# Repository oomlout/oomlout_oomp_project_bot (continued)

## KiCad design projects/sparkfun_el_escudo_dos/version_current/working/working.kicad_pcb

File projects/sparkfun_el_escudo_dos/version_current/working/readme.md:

# EL_Escudo_Dos by sparkfun  
This is a harvested standardized copy of a project from github.  
The original project can be found at:  
https://github.com/sparkfun/EL_Escudo_Dos  
Please consult that link for additional, details, files, and license information.  
Note: It was auto harvested and if the original repo had more than one board file or anything out of the ordinary the files here are likely not representative.

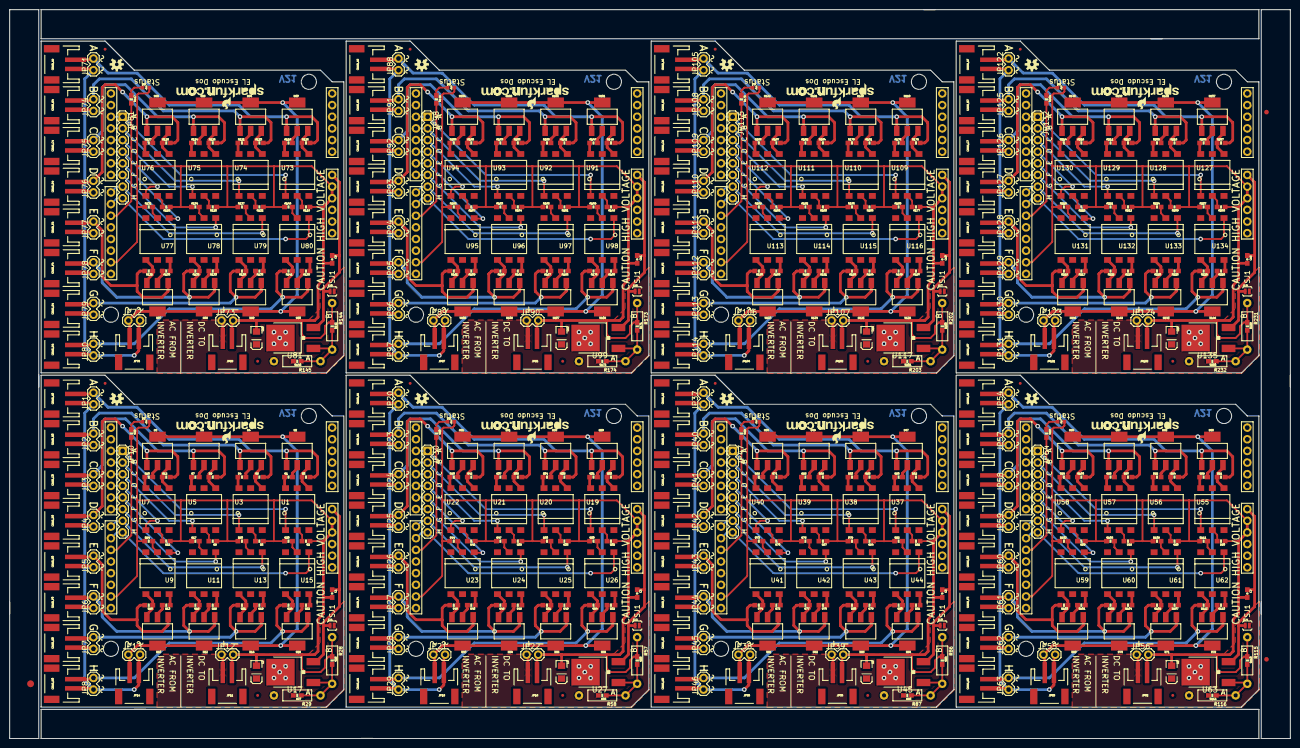
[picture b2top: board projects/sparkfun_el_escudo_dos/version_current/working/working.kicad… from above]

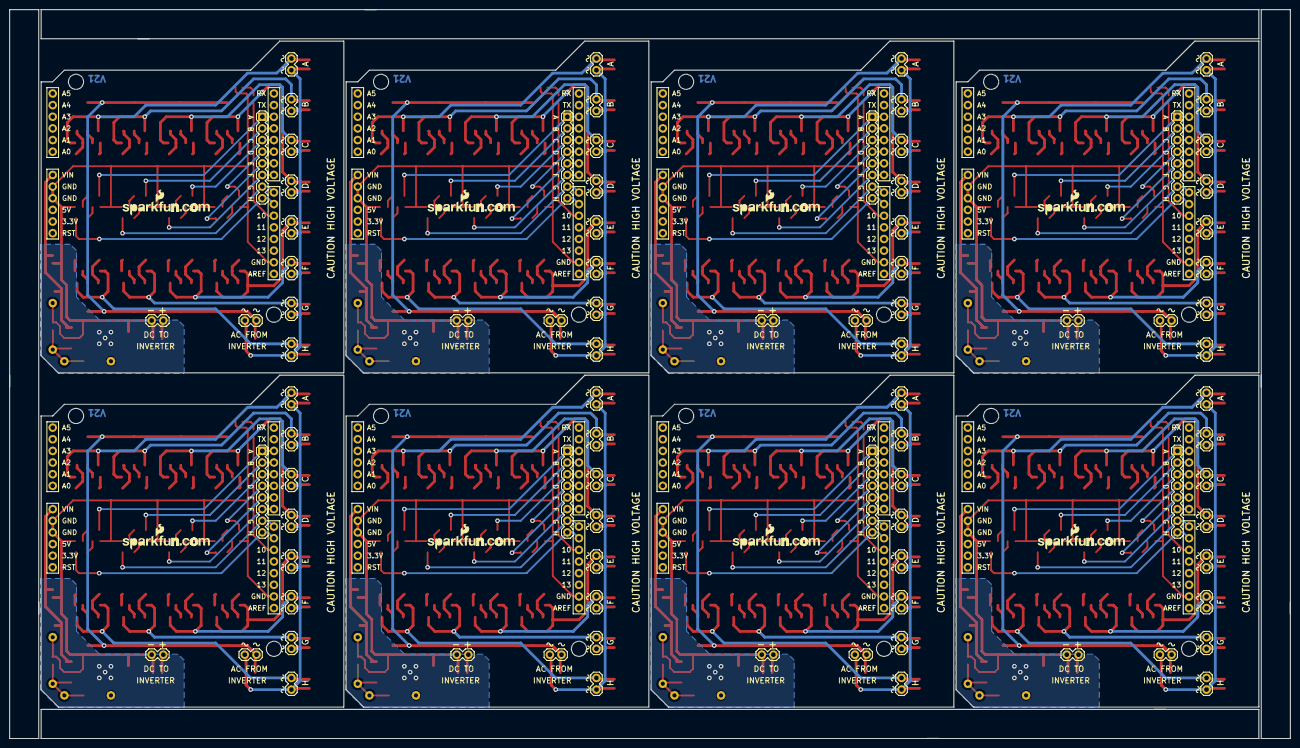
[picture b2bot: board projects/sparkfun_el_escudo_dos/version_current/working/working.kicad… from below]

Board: 2 copper layers, 279.4 x 159.0 mm, 619 parts (8 on the bottom side), 448 nets.

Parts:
C1, C3, C5, C7, C9, C11, C13, C15: 0.1uF; 0603-CAP
C2, C4, C6, C8, C10, C12, C14, C16: 10uF; EIA3216
CHAN_A0, CHAN_A1, CHAN_A2, CHAN_A3, CHAN_A4, CHAN_A5, CHAN_A6, CHAN_A7: JST-2-SMD
CHAN_B0, CHAN_B1, CHAN_B2, CHAN_B3, CHAN_B4, CHAN_B5, CHAN_B6, CHAN_B7: JST-2-SMD
CHAN_C0, CHAN_C1, CHAN_C2, CHAN_C3, CHAN_C4, CHAN_C5, CHAN_C6, CHAN_C7: JST-2-SMD
CHAN_D0, CHAN_D1, CHAN_D2, CHAN_D3, CHAN_D4, CHAN_D5, CHAN_D6, CHAN_D7: JST-2-SMD
CHAN_E0, CHAN_E1, CHAN_E2, CHAN_E3, CHAN_E4, CHAN_E5, CHAN_E6, CHAN_E7: JST-2-SMD
CHAN_F0, CHAN_F1, CHAN_F2, CHAN_F3, CHAN_F4, CHAN_F5, CHAN_F6, CHAN_F7: JST-2-SMD
CHAN_G0, CHAN_G1, CHAN_G2, CHAN_G3, CHAN_G4, CHAN_G5, CHAN_G6, CHAN_G7: JST-2-SMD
CHAN_H0, CHAN_H1, CHAN_H2, CHAN_H3, CHAN_H4, CHAN_H5, CHAN_H6, CHAN_H7: JST-2-SMD
D1, D2, D3, D4, D5, D6, D7, D8: Status; LED-0603
E$1: FIDUCIAL-1.5X3
E$5, E$6: FIDUCIAL-1X2
JP1, JP2, JP3, JP4, JP5, JP6, JP7, JP8, JP12, JP13, JP20, JP21, JP22, JP23, JP24, JP25, JP26, JP27, JP28, JP29, JP37, JP38, JP39, JP40, JP41, JP42, JP43, JP44, JP45, JP46, JP54, JP55, JP56, JP57, JP58, JP59, JP60, JP61, JP62, JP63, JP71, JP72, JP73, JP74, JP75, JP76, JP77, JP78, JP79, JP80, JP88, JP89, JP90, JP91, JP92, JP93, JP94, JP95, JP96, JP97, JP105, JP106, JP107, JP108, JP109, JP110, JP111, JP112, JP113, JP114, JP122, JP123, JP124, JP125, JP126, JP127, JP128, JP129, JP130, JP131: 1X02
JP9, JP15, JP31, JP32, JP48, JP49, JP65, JP66, JP82, JP83, JP99, JP100, JP116, JP117, JP133, JP134: LOGO-SFENEW; SFE-NEW-WEBLOGO
JP10, JP30, JP47, JP64, JP81, JP98, JP115, JP132: 1X08
JP11, JP14, JP18, JP19, JP35, JP36, JP52, JP53, JP69, JP70, JP86, JP87, JP103, JP104, JP120, JP121: JST-2-SMD
JP16, JP17, JP33, JP34, JP50, JP51, JP67, JP68, JP84, JP85, JP101, JP102, JP118, JP119, JP135, JP136: FIDUCIALUFIDUCIAL; MICRO-FIDUCIAL
R1, R3, R4, R6, R7, R9, R10, R12, R13, R15, R16, R18, R19, R21, R22, R24, R25, R30, R31, R33, R34, R36, R37, R39, R40, R42, R43, R45, R46, R48, R49, R51, R52, R54, R59, R60, R62, R63, R65, R66, R68, R69, R71, R72, R74, R75, R77, R78, R80, R81, R83, R88, R89, R91, R92, R94, R95, R97, R98, R100, R101, R103, R104, R106, R107, R109, R110, R112, R117, R118, R120, R121, R123, R124, R126, R127, R129, R130, R132, R133, R135, R136, R138, R139, R141, R146, R147, R149, R150, R152, R153, R155, R156, R158, R159, R161, R162, R164, R165, R167, R168, R170, R175, R176, R178, R179, R181, R182, R184, R185, R187, R188, R190, R191, R193, R194, R196, R197, R199, R204, R205, R207, R208, R210, R211, R213, R214, R216, R217, R219, R220, R222, R223, R225, R226, R228: 330; 0603-RES
R2, R5, R8, R11, R14, R17, R20, R23, R26, R32, R35, R38, R41, R44, R47, R50, R53, R55, R61, R64, R67, R70, R73, R76, R79, R82, R84, R90, R93, R96, R99, R102, R105, R108, R111, R113, R119, R122, R125, R128, R131, R134, R137, R140, R142, R148, R151, R154, R157, R160, R163, R166, R169, R171, R177, R180, R183, R186, R189, R192, R195, R198, R200, R206, R209, R212, R215, R218, R221, R224, R227, R229: 390; 0603-RES
R27, R56, R85, R114, R143, R172, R201, R230: 240; 0603-RES
R28, R57, R86, R115, R144, R173, R202, R231: B; AXIAL-0.4
R29, R58, R87, R116, R145, R174, R203, R232: A; AXIAL-0.4
SJ1, SJ2, SJ3, SJ4, SJ5, SJ6, SJ7, SJ8: SJ_2S-NO
U1, U3, U5, U7, U9, U11, U13, U15, U19, U20, U21, U22, U23, U24, U25, U26, U37, U38, U39, U40, U41, U42, U43, U44, U55, U56, U57, U58, U59, U60, U61, U62, U73, U74, U75, U76, U77, U78, U79, U80, U91, U92, U93, U94, U95, U96, U97, U98, U109, U110, U111, U112, U113, U114, U115, U116, U127, U128, U129, U130, U131, U132, U133, U134: MOC3063S; DIP8SMD
U2, U4, U6, U8, U10, U12, U14, U16, U29, U30, U31, U32, U33, U34, U35, U36, U47, U48, U49, U50, U51, U52, U53, U54, U65, U66, U67, U68, U69, U70, U71, U72, U83, U84, U85, U86, U87, U88, U89, U90, U101, U102, U103, U104, U105, U106, U107, U108, U119, U120, U121, U122, U123, U124, U125, U126, U137, U138, U139, U140, U141, U142, U143, U144: Z0103MN; SOT223
U17, U27, U45, U63, U81, U99, U117, U135: LM317; V-REG_DPACK
U18, U28, U46, U64, U82, U100, U118, U136: ARDUINO_SHIELD; DUEMILANOVE_SHIELD_NOLABELS
U$1, U$2, U$3, U$4, U$5, U$6, U$7, U$8: OSHW-LOGOS; OSHW-LOGO-S

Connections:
EL_A: JP10.1, U1.1, U18.D2
EL_A1: JP30.1, U19.1, U28.D2
EL_A2: JP47.1, U37.1, U46.D2
EL_A3: JP64.1, U55.1, U64.D2
EL_A4: JP81.1, U73.1, U82.D2
EL_A5: JP98.1, U91.1, U100.D2
EL_A6: JP115.1, U109.1, U118.D2
EL_A7: JP132.1, U127.1, U136.D2
EL_B: JP10.2, U3.1, U18.D3
EL_B1: JP30.2, U20.1, U28.D3
EL_B2: JP47.2, U38.1, U46.D3
EL_B3: JP64.2, U56.1, U64.D3
EL_B4: JP81.2, U74.1, U82.D3
EL_B5: JP98.2, U92.1, U100.D3
EL_B6: JP115.2, U110.1, U118.D3
EL_B7: JP132.2, U128.1, U136.D3
EL_C: JP10.3, U5.1, U18.D4
EL_C1: JP30.3, U21.1, U28.D4
EL_C2: JP47.3, U39.1, U46.D4
EL_C3: JP64.3, U57.1, U64.D4
EL_C4: JP81.3, U75.1, U82.D4
EL_C5: JP98.3, U93.1, U100.D4
EL_C6: JP115.3, U111.1, U118.D4
EL_C7: JP132.3, U129.1, U136.D4
EL_D: JP10.4, U7.1, U18.D5
EL_D1: JP30.4, U22.1, U28.D5
EL_D2: JP47.4, U40.1, U46.D5
EL_D3: JP64.4, U58.1, U64.D5
EL_D4: JP81.4, U76.1, U82.D5
EL_D5: JP98.4, U94.1, U100.D5
EL_D6: JP115.4, U112.1, U118.D5
EL_D7: JP132.4, U130.1, U136.D5
EL_E: JP10.5, U9.1, U18.D6
EL_E1: JP30.5, U23.1, U28.D6
EL_E2: JP47.5, U41.1, U46.D6
EL_E3: JP64.5, U59.1, U64.D6
EL_E4: JP81.5, U77.1, U82.D6
EL_E5: JP98.5, U95.1, U100.D6
EL_E6: JP115.5, U113.1, U118.D6
EL_E7: JP132.5, U131.1, U136.D6
EL_F: JP10.6, U11.1, U18.D7
EL_F1: JP30.6, U24.1, U28.D7
EL_F2: JP47.6, U42.1, U46.D7
EL_F3: JP64.6, U60.1, U64.D7
EL_F4: JP81.6, U78.1, U82.D7
EL_F5: JP98.6, U96.1, U100.D7
EL_F6: JP115.6, U114.1, U118.D7
EL_F7: JP132.6, U132.1, U136.D7
EL_G: JP10.7, U13.1, U18.D8
EL_G1: JP30.7, U25.1, U28.D8
EL_G2: JP47.7, U43.1, U46.D8
EL_G3: JP64.7, U61.1, U64.D8
EL_G4: JP81.7, U79.1, U82.D8
EL_G5: JP98.7, U97.1, U100.D8
EL_G6: JP115.7, U115.1, U118.D8
EL_G7: JP132.7, U133.1, U136.D8
EL_H: JP10.8, U15.1, U18.D9
EL_H1: JP30.8, U26.1, U28.D9
EL_H2: JP47.8, U44.1, U46.D9
EL_H3: JP64.8, U62.1, U64.D9
EL_H4: JP81.8, U80.1, U82.D9
EL_H5: JP98.8, U98.1, U100.D9
EL_H6: JP115.8, U116.1, U118.D9
EL_H7: JP132.8, U134.1, U136.D9
GND: C1.2, C2.C, D1.C, JP11.1, JP12.2, R2.1, R5.1, R8.1, R11.1, R14.1, R17.1, R20.1, R23.1, R26.1, R28.P$1, U18.GND@0, U18.GND@1, U18.GND@2
GND1: C3.2, C4.C, D2.C, JP18.1, JP22.2, R32.1, R35.1, R38.1, R41.1, R44.1, R47.1, R50.1, R53.1, R55.1, R57.P$1, U28.GND@0, U28.GND@1, U28.GND@2
GND2: C5.2, C6.C, D3.C, JP35.1, JP39.2, R61.1, R64.1, R67.1, R70.1, R73.1, R76.1, R79.1, R82.1, R84.1, R86.P$1, U46.GND@0, U46.GND@1, U46.GND@2
GND3: C7.2, C8.C, D4.C, JP52.1, JP56.2, R90.1, R93.1, R96.1, R99.1, R102.1, R105.1, R108.1, R111.1, R113.1, R115.P$1, U64.GND@0, U64.GND@1, U64.GND@2
GND4: C9.2, C10.C, D5.C, JP69.1, JP73.2, R119.1, R122.1, R125.1, R128.1, R131.1, R134.1, R137.1, R140.1, R142.1, R144.P$1, U82.GND@0, U82.GND@1, U82.GND@2
GND5: C11.2, C12.C, D6.C, JP86.1, JP90.2, R148.1, R151.1, R154.1, R157.1, R160.1, R163.1, R166.1, R169.1, R171.1, R173.P$1, U100.GND@0, U100.GND@1, U100.GND@2
GND6: C13.2, C14.C, D7.C, JP103.1, JP107.2, R177.1, R180.1, R183.1, R186.1, R189.1, R192.1, R195.1, R198.1, R200.1, R202.P$1, U118.GND@0, U118.GND@1, U118.GND@2
GND7: C15.2, C16.C, D8.C, JP120.1, JP124.2, R206.1, R209.1, R212.1, R215.1, R218.1, R221.1, R224.1, R227.1, R229.1, R231.P$1, U136.GND@0, U136.GND@1, U136.GND@2
HV: JP13.1, JP14.2, U2.4, U4.4, U6.4, U8.4, U10.4, U12.4, U14.4, U16.4
HV1: JP19.2, JP21.1, U29.4, U30.4, U31.4, U32.4, U33.4, U34.4, U35.4, U36.4
HV2: JP36.2, JP38.1, U47.4, U48.4, U49.4, U50.4, U51.4, U52.4, U53.4, U54.4
HV3: JP53.2, JP55.1, U65.4, U66.4, U67.4, U68.4, U69.4, U70.4, U71.4, U72.4
HV4: JP70.2, JP72.1, U83.4, U84.4, U85.4, U86.4, U87.4, U88.4, U89.4, U90.4
HV5: JP87.2, JP89.1, U101.4, U102.4, U103.4, U104.4, U105.4, U106.4, U107.4, U108.4
HV6: JP104.2, JP106.1, U119.4, U120.4, U121.4, U122.4, U123.4, U124.4, U125.4, U126.4
HV7: JP121.2, JP123.1, U137.4, U138.4, U139.4, U140.4, U141.4, U142.4, U143.4, U144.4
HVGND: CHAN_A0.1, CHAN_B0.1, CHAN_C0.1, CHAN_D0.1, CHAN_E0.1, CHAN_F0.1, CHAN_G0.1, CHAN_H0.1, JP1.1, JP2.1, JP3.1, JP4.1, JP5.1, JP6.1, JP7.1, JP8.1, JP13.2, JP14.1
HVGND1: CHAN_A1.1, CHAN_B1.1, CHAN_C1.1, CHAN_D1.1, CHAN_E1.1, CHAN_F1.1, CHAN_G1.1, CHAN_H1.1, JP19.1, JP20.1, JP21.2, JP23.1, JP24.1, JP25.1, JP26.1, JP27.1, JP28.1, JP29.1
HVGND2: CHAN_A2.1, CHAN_B2.1, CHAN_C2.1, CHAN_D2.1, CHAN_E2.1, CHAN_F2.1, CHAN_G2.1, CHAN_H2.1, JP36.1, JP37.1, JP38.2, JP40.1, JP41.1, JP42.1, JP43.1, JP44.1, JP45.1, JP46.1
HVGND3: CHAN_A3.1, CHAN_B3.1, CHAN_C3.1, CHAN_D3.1, CHAN_E3.1, CHAN_F3.1, CHAN_G3.1, CHAN_H3.1, JP53.1, JP54.1, JP55.2, JP57.1, JP58.1, JP59.1, JP60.1, JP61.1, JP62.1, JP63.1
HVGND4: CHAN_A4.1, CHAN_B4.1, CHAN_C4.1, CHAN_D4.1, CHAN_E4.1, CHAN_F4.1, CHAN_G4.1, CHAN_H4.1, JP70.1, JP71.1, JP72.2, JP74.1, JP75.1, JP76.1, JP77.1, JP78.1, JP79.1, JP80.1
HVGND5: CHAN_A5.1, CHAN_B5.1, CHAN_C5.1, CHAN_D5.1, CHAN_E5.1, CHAN_F5.1, CHAN_G5.1, CHAN_H5.1, JP87.1, JP88.1, JP89.2, JP91.1, JP92.1, JP93.1, JP94.1, JP95.1, JP96.1, JP97.1
HVGND6: CHAN_A6.1, CHAN_B6.1, CHAN_C6.1, CHAN_D6.1, CHAN_E6.1, CHAN_F6.1, CHAN_G6.1, CHAN_H6.1, JP104.1, JP105.1, JP106.2, JP108.1, JP109.1, JP110.1, JP111.1, JP112.1, JP113.1, JP114.1
HVGND7: CHAN_A7.1, CHAN_B7.1, CHAN_C7.1, CHAN_D7.1, CHAN_E7.1, CHAN_F7.1, CHAN_G7.1, CHAN_H7.1, JP121.1, JP122.1, JP123.2, JP125.1, JP126.1, JP127.1, JP128.1, JP129.1, JP130.1, JP131.1
INV: C2.A, JP11.2, JP12.1, R27.2, R29.P$2, SJ1.2, U17.4
INV1: C4.A, JP18.2, JP22.1, R56.2, R58.P$2, SJ2.2, U27.4
INV2: C6.A, JP35.2, JP39.1, R85.2, R87.P$2, SJ3.2, U45.4
INV3: C8.A, JP52.2, JP56.1, R114.2, R116.P$2, SJ4.2, U63.4
INV4: C10.A, JP69.2, JP73.1, R143.2, R145.P$2, SJ5.2, U81.4
INV5: C12.A, JP86.2, JP90.1, R172.2, R174.P$2, SJ6.2, U99.4
INV6: C14.A, JP103.2, JP107.1, R201.2, R203.P$2, SJ7.2, U117.4
INV7: C16.A, JP120.2, JP124.1, R230.2, R232.P$2, SJ8.2, U135.4
unnamed: R2.2, U1.2
unnamed: R26.2, R27.1, R28.P$2, R29.P$1, U17.1
unnamed: R1.1, U1.6
unnamed: R25.2, U18.D10
unnamed: R6.1, U3.4, U4.3
unnamed: R5.2, U3.2
unnamed: R4.1, U3.6
unnamed: CHAN_B0.2, JP2.2, R6.2, U4.1
unnamed: R1.2, U2.2
unnamed: R9.1, U5.4, U6.3
unnamed: R8.2, U5.2
unnamed: R7.1, U5.6
unnamed: CHAN_C0.2, JP3.2, R9.2, U6.1
unnamed: D1.A, R25.1
unnamed: R4.2, U4.2
unnamed: R12.1, U7.4, U8.3
unnamed: R11.2, U7.2
unnamed: R10.1, U7.6
unnamed: CHAN_D0.2, JP4.2, R12.2, U8.1
unnamed: R7.2, U6.2
unnamed: CHAN_A0.2, JP1.2, R3.2, U2.1
unnamed: R15.1, U9.4, U10.3
unnamed: R14.2, U9.2
unnamed: R13.1, U9.6
unnamed: CHAN_E0.2, JP5.2, R15.2, U10.1
unnamed: R10.2, U8.2
unnamed: R18.1, U11.4, U12.3
unnamed: R17.2, U11.2
unnamed: R16.1, U11.6
unnamed: CHAN_F0.2, JP6.2, R18.2, U12.1
unnamed: R13.2, U10.2
unnamed: R21.1, U13.4, U14.3
unnamed: R20.2, U13.2
unnamed: R19.1, U13.6
unnamed: CHAN_G0.2, JP7.2, R21.2, U14.1
unnamed: R16.2, U12.2
unnamed: R24.1, U15.4, U16.3
unnamed: R23.2, U15.2
unnamed: R22.1, U15.6
unnamed: CHAN_H0.2, JP8.2, R24.2, U16.1
unnamed: R19.2, U14.2
unnamed: R22.2, U16.2
unnamed: D2.A, R30.1
unnamed: R33.1, U19.4, U29.3
unnamed: R32.2, U19.2
unnamed: R31.1, U19.6
unnamed: CHAN_A1.2, JP20.2, R33.2, U29.1
unnamed: R36.1, U20.4, U30.3
unnamed: R35.2, U20.2
unnamed: R34.1, U20.6
unnamed: CHAN_B1.2, JP23.2, R36.2, U30.1
unnamed: R39.1, U21.4, U31.3
unnamed: R38.2, U21.2
unnamed: R37.1, U21.6
unnamed: CHAN_C1.2, JP24.2, R39.2, U31.1
unnamed: R42.1, U22.4, U32.3
unnamed: R41.2, U22.2
unnamed: R40.1, U22.6
unnamed: CHAN_D1.2, JP25.2, R42.2, U32.1
unnamed: R45.1, U23.4, U33.3
unnamed: R44.2, U23.2
unnamed: R43.1, U23.6
unnamed: CHAN_E1.2, JP26.2, R45.2, U33.1
unnamed: R48.1, U24.4, U34.3
unnamed: R47.2, U24.2
unnamed: R46.1, U24.6
unnamed: CHAN_F1.2, JP27.2, R48.2, U34.1
unnamed: R51.1, U25.4, U35.3
unnamed: R50.2, U25.2
unnamed: R49.1, U25.6
unnamed: CHAN_G1.2, JP28.2, R51.2, U35.1
unnamed: R54.1, U26.4, U36.3
unnamed: R53.2, U26.2
unnamed: R52.1, U26.6
unnamed: CHAN_H1.2, JP29.2, R54.2, U36.1
unnamed: R55.2, R56.1, R57.P$2, R58.P$1, U27.1
unnamed: R31.2, U29.2
unnamed: R34.2, U30.2
unnamed: R37.2, U31.2
unnamed: R40.2, U32.2
unnamed: R43.2, U33.2
unnamed: R46.2, U34.2
unnamed: R49.2, U35.2
unnamed: R52.2, U36.2
unnamed: R30.2, U28.D10
unnamed: D3.A, R59.1
unnamed: R62.1, U37.4, U47.3
unnamed: R61.2, U37.2
unnamed: R60.1, U37.6
unnamed: CHAN_A2.2, JP37.2, R62.2, U47.1
unnamed: R65.1, U38.4, U48.3
unnamed: R64.2, U38.2
unnamed: R63.1, U38.6
unnamed: CHAN_B2.2, JP40.2, R65.2, U48.1
unnamed: R68.1, U39.4, U49.3
unnamed: R67.2, U39.2
unnamed: R66.1, U39.6
unnamed: CHAN_C2.2, JP41.2, R68.2, U49.1
unnamed: R71.1, U40.4, U50.3
unnamed: R70.2, U40.2
unnamed: R69.1, U40.6
unnamed: CHAN_D2.2, JP42.2, R71.2, U50.1
unnamed: R74.1, U41.4, U51.3
unnamed: R73.2, U41.2
unnamed: R72.1, U41.6
unnamed: CHAN_E2.2, JP43.2, R74.2, U51.1
unnamed: R77.1, U42.4, U52.3
unnamed: R76.2, U42.2
unnamed: R75.1, U42.6
unnamed: CHAN_F2.2, JP44.2, R77.2, U52.1
unnamed: R80.1, U43.4, U53.3
unnamed: R79.2, U43.2
unnamed: R78.1, U43.6
unnamed: CHAN_G2.2, JP45.2, R80.2, U53.1
unnamed: R83.1, U44.4, U54.3
unnamed: R82.2, U44.2
unnamed: R3.1, U1.4, U2.3
unnamed: R81.1, U44.6
unnamed: CHAN_H2.2, JP46.2, R83.2, U54.1
unnamed: R84.2, R85.1, R86.P$2, R87.P$1, U45.1
unnamed: R60.2, U47.2
unnamed: R63.2, U48.2
unnamed: R66.2, U49.2
unnamed: R69.2, U50.2
unnamed: R72.2, U51.2
unnamed: R75.2, U52.2
unnamed: R78.2, U53.2
unnamed: R81.2, U54.2
unnamed: R59.2, U46.D10
unnamed: D4.A, R88.1
unnamed: R91.1, U55.4, U65.3
unnamed: R90.2, U55.2
unnamed: R89.1, U55.6
unnamed: CHAN_A3.2, JP54.2, R91.2, U65.1
unnamed: R94.1, U56.4, U66.3
unnamed: R93.2, U56.2
unnamed: R92.1, U56.6
unnamed: CHAN_B3.2, JP57.2, R94.2, U66.1
unnamed: R97.1, U57.4, U67.3
unnamed: R96.2, U57.2
unnamed: R95.1, U57.6
unnamed: CHAN_C3.2, JP58.2, R97.2, U67.1
unnamed: R100.1, U58.4, U68.3
unnamed: R99.2, U58.2
unnamed: R98.1, U58.6
unnamed: CHAN_D3.2, JP59.2, R100.2, U68.1
unnamed: R103.1, U59.4, U69.3
unnamed: R102.2, U59.2
unnamed: R101.1, U59.6
unnamed: CHAN_E3.2, JP60.2, R103.2, U69.1
unnamed: R106.1, U60.4, U70.3
unnamed: R105.2, U60.2
unnamed: R104.1, U60.6
unnamed: CHAN_F3.2, JP61.2, R106.2, U70.1
unnamed: R109.1, U61.4, U71.3
unnamed: R108.2, U61.2
unnamed: R107.1, U61.6
unnamed: CHAN_G3.2, JP62.2, R109.2, U71.1
unnamed: R112.1, U62.4, U72.3
unnamed: R111.2, U62.2
unnamed: R110.1, U62.6
unnamed: CHAN_H3.2, JP63.2, R112.2, U72.1
unnamed: R113.2, R114.1, R115.P$2, R116.P$1, U63.1
unnamed: R89.2, U65.2
unnamed: R92.2, U66.2
unnamed: R95.2, U67.2
unnamed: R98.2, U68.2
unnamed: R101.2, U69.2
unnamed: R104.2, U70.2
unnamed: R107.2, U71.2
unnamed: R110.2, U72.2
unnamed: R88.2, U64.D10
unnamed: D5.A, R117.1
unnamed: R120.1, U73.4, U83.3
unnamed: R119.2, U73.2
unnamed: R118.1, U73.6
unnamed: CHAN_A4.2, JP71.2, R120.2, U83.1
unnamed: R123.1, U74.4, U84.3
unnamed: R122.2, U74.2
unnamed: R121.1, U74.6
unnamed: CHAN_B4.2, JP74.2, R123.2, U84.1
unnamed: R126.1, U75.4, U85.3
unnamed: R125.2, U75.2
unnamed: R124.1, U75.6
unnamed: CHAN_C4.2, JP75.2, R126.2, U85.1
unnamed: R129.1, U76.4, U86.3
unnamed: R128.2, U76.2
unnamed: R127.1, U76.6
unnamed: CHAN_D4.2, JP76.2, R129.2, U86.1
unnamed: R132.1, U77.4, U87.3
unnamed: R131.2, U77.2
unnamed: R130.1, U77.6
unnamed: CHAN_E4.2, JP77.2, R132.2, U87.1
unnamed: R135.1, U78.4, U88.3
unnamed: R134.2, U78.2
unnamed: R133.1, U78.6
unnamed: CHAN_F4.2, JP78.2, R135.2, U88.1
unnamed: R138.1, U79.4, U89.3
unnamed: R137.2, U79.2
unnamed: R136.1, U79.6
unnamed: CHAN_G4.2, JP79.2, R138.2, U89.1
unnamed: R141.1, U80.4, U90.3
unnamed: R140.2, U80.2
unnamed: R139.1, U80.6
unnamed: CHAN_H4.2, JP80.2, R141.2, U90.1
unnamed: R142.2, R143.1, R144.P$2, R145.P$1, U81.1
unnamed: R118.2, U83.2
unnamed: R121.2, U84.2
unnamed: R124.2, U85.2
unnamed: R127.2, U86.2
unnamed: R130.2, U87.2
unnamed: R133.2, U88.2
unnamed: R136.2, U89.2
unnamed: R139.2, U90.2
unnamed: R117.2, U82.D10
unnamed: D6.A, R146.1
unnamed: R149.1, U91.4, U101.3
unnamed: R148.2, U91.2
unnamed: R147.1, U91.6
unnamed: CHAN_A5.2, JP88.2, R149.2, U101.1
unnamed: R152.1, U92.4, U102.3
unnamed: R151.2, U92.2
unnamed: R150.1, U92.6
unnamed: CHAN_B5.2, JP91.2, R152.2, U102.1
unnamed: R155.1, U93.4, U103.3
unnamed: R154.2, U93.2
unnamed: R153.1, U93.6
unnamed: CHAN_C5.2, JP92.2, R155.2, U103.1
unnamed: R158.1, U94.4, U104.3
unnamed: R157.2, U94.2
unnamed: R156.1, U94.6
unnamed: CHAN_D5.2, JP93.2, R158.2, U104.1
unnamed: R161.1, U95.4, U105.3
unnamed: R160.2, U95.2
unnamed: R159.1, U95.6
unnamed: CHAN_E5.2, JP94.2, R161.2, U105.1
unnamed: R164.1, U96.4, U106.3
unnamed: R163.2, U96.2
unnamed: R162.1, U96.6
unnamed: CHAN_F5.2, JP95.2, R164.2, U106.1
unnamed: R167.1, U97.4, U107.3
unnamed: R166.2, U97.2
unnamed: R165.1, U97.6
unnamed: CHAN_G5.2, JP96.2, R167.2, U107.1
unnamed: R170.1, U98.4, U108.3
unnamed: R169.2, U98.2
unnamed: R168.1, U98.6
unnamed: CHAN_H5.2, JP97.2, R170.2, U108.1
unnamed: R171.2, R172.1, R173.P$2, R174.P$1, U99.1
unnamed: R147.2, U101.2
unnamed: R150.2, U102.2
unnamed: R153.2, U103.2
unnamed: R156.2, U104.2
unnamed: R159.2, U105.2
unnamed: R162.2, U106.2
unnamed: R165.2, U107.2
unnamed: R168.2, U108.2
unnamed: R146.2, U100.D10
unnamed: D7.A, R175.1
unnamed: R178.1, U109.4, U119.3
unnamed: R177.2, U109.2
unnamed: R176.1, U109.6
unnamed: CHAN_A6.2, JP105.2, R178.2, U119.1
unnamed: R181.1, U110.4, U120.3
unnamed: R180.2, U110.2
unnamed: R179.1, U110.6
unnamed: CHAN_B6.2, JP108.2, R181.2, U120.1
unnamed: R184.1, U111.4, U121.3
unnamed: R183.2, U111.2
unnamed: R182.1, U111.6
unnamed: CHAN_C6.2, JP109.2, R184.2, U121.1
unnamed: R187.1, U112.4, U122.3
unnamed: R186.2, U112.2
unnamed: R185.1, U112.6
unnamed: CHAN_D6.2, JP110.2, R187.2, U122.1
unnamed: R190.1, U113.4, U123.3
unnamed: R189.2, U113.2
unnamed: R188.1, U113.6
unnamed: CHAN_E6.2, JP111.2, R190.2, U123.1
unnamed: R193.1, U114.4, U124.3
unnamed: R192.2, U114.2
unnamed: R191.1, U114.6
unnamed: CHAN_F6.2, JP112.2, R193.2, U124.1
unnamed: R196.1, U115.4, U125.3
unnamed: R195.2, U115.2
unnamed: R194.1, U115.6
unnamed: CHAN_G6.2, JP113.2, R196.2, U125.1
unnamed: R199.1, U116.4, U126.3
unnamed: R198.2, U116.2
unnamed: R197.1, U116.6
unnamed: CHAN_H6.2, JP114.2, R199.2, U126.1
unnamed: R200.2, R201.1, R202.P$2, R203.P$1, U117.1
unnamed: R176.2, U119.2
unnamed: R179.2, U120.2
unnamed: R182.2, U121.2
unnamed: R185.2, U122.2
unnamed: R188.2, U123.2
unnamed: R191.2, U124.2
unnamed: R194.2, U125.2
unnamed: R197.2, U126.2
unnamed: R175.2, U118.D10
unnamed: D8.A, R204.1
unnamed: R207.1, U127.4, U137.3
unnamed: R206.2, U127.2
unnamed: R205.1, U127.6
unnamed: CHAN_A7.2, JP122.2, R207.2, U137.1
unnamed: R210.1, U128.4, U138.3
unnamed: R209.2, U128.2
unnamed: R208.1, U128.6
unnamed: CHAN_B7.2, JP125.2, R210.2, U138.1
unnamed: R213.1, U129.4, U139.3
unnamed: R212.2, U129.2
unnamed: R211.1, U129.6
unnamed: CHAN_C7.2, JP126.2, R213.2, U139.1
unnamed: R216.1, U130.4, U140.3
unnamed: R215.2, U130.2
unnamed: R214.1, U130.6
unnamed: CHAN_D7.2, JP127.2, R216.2, U140.1
unnamed: R219.1, U131.4, U141.3
unnamed: R218.2, U131.2
unnamed: R217.1, U131.6
unnamed: CHAN_E7.2, JP128.2, R219.2, U141.1
unnamed: R222.1, U132.4, U142.3
unnamed: R221.2, U132.2
unnamed: R220.1, U132.6
unnamed: CHAN_F7.2, JP129.2, R222.2, U142.1
unnamed: R225.1, U133.4, U143.3
unnamed: R224.2, U133.2
unnamed: R223.1, U133.6
unnamed: CHAN_G7.2, JP130.2, R225.2, U143.1
unnamed: R228.1, U134.4, U144.3
unnamed: R227.2, U134.2
unnamed: R226.1, U134.6
unnamed: CHAN_H7.2, JP131.2, R228.2, U144.1
unnamed: R229.2, R230.1, R231.P$2, R232.P$1, U135.1
unnamed: R205.2, U137.2
unnamed: R208.2, U138.2
unnamed: R211.2, U139.2
unnamed: R214.2, U140.2
unnamed: R217.2, U141.2
unnamed: R220.2, U142.2
unnamed: R223.2, U143.2
unnamed: R226.2, U144.2
unnamed: R204.2, U136.D10
RAW: C1.1, SJ1.1, U17.3, U18.VIN
RAW1: C3.1, SJ2.1, U27.3, U28.VIN
RAW2: C5.1, SJ3.1, U45.3, U46.VIN
RAW3: C7.1, SJ4.1, U63.3, U64.VIN
RAW4: C9.1, SJ5.1, U81.3, U82.VIN
RAW5: C11.1, SJ6.1, U99.3, U100.VIN
RAW6: C13.1, SJ7.1, U117.3, U118.VIN
RAW7: C15.1, SJ8.1, U135.3, U136.VIN

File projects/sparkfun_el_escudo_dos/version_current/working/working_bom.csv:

"Id";"Designator";"Footprint";"Quantity";"Designation";"Supplier and ref";
1;"R58,R87,R29,R174,R145,R203,R116,R232";"AXIAL-0.4";8;"A";;;
2;"R216,R175,R12,R40,R69,R39,R146,R94,R127,R184,R150,R74,R118,R178,R219,R124,R159,R109,R106,R36,R88,R181,R22,R136,R104,R37,R170,R91,R205,R126,R45,R211,R226,R19,R149,R139,R156,R199,R185,R112,R97,R117,R153,R217,R43,R3,R147,R92,R72,R71,R141,R10,R100,R225,R204,R42,R161,R123,R228,R191,R138,R62,R194,R193,R168,R1,R81,R15,R179,R7,R46,R80,R83,R162,R13,R196,R78,R188,R164,R133,R16,R51,R167,R54,R132,R98,R34,R107,R4,R60,R207,R75,R176,R65,R25,R101,R120,R18,R49,R89,R210,R222,R165,R21,R33,R77,R213,R110,R95,R24,R68,R135,R182,R152,R121,R190,R197,R223,R155,R6,R103,R48,R208,R130,R31,R158,R220,R214,R187,R66,R9,R59,R63,R52,R129,R30";"0603-RES";136;"330";;;
3;"JP30,JP132,JP47,JP81,JP64,JP10,JP98,JP115";"1X08";8;"";;;
4;"JP21,JP110,JP27,JP127,JP3,JP29,JP45,JP25,JP105,JP22,JP128,JP109,JP107,JP46,JP125,JP91,JP5,JP4,JP97,JP26,JP28,JP43,JP131,JP59,JP56,JP92,JP13,JP88,JP8,JP7,JP61,JP112,JP113,JP2,JP57,JP1,JP80,JP79,JP108,JP54,JP37,JP73,JP44,JP40,JP74,JP122,JP106,JP71,JP90,JP12,JP58,JP111,JP6,JP42,JP39,JP78,JP129,JP130,JP20,JP94,JP126,JP60,JP63,JP23,JP95,JP96,JP38,JP123,JP124,JP76,JP24,JP72,JP41,JP93,JP89,JP77,JP114,JP62,JP75,JP55";"1X02";80;"";;;
5;"R115,R231,R202,R28,R57,R173,R86,R144";"AXIAL-0.4";8;"B";;;
6;"C1,C13,C9,C7,C5,C15,C11,C3";"0603-CAP";8;"0.1uF";;;
7;"R131,R189,R44,R26,R50,R23,R38,R151,R96,R79,R224,R102,R177,R17,R61,R183,R142,R163,R137,R76,R8,R195,R53,R198,R157,R154,R218,R209,R70,R11,R186,R206,R227,R160,R90,R221,R55,R140,R41,R84,R14,R113,R148,R32,R134,R200,R192,R169,R215,R122,R73,R20,R128,R67,R93,R105,R5,R119,R108,R64,R35,R166,R82,R229,R125,R212,R180,R2,R99,R171,R47,R111";"0603-RES";72;"390";;;
8;"JP101,JP119,JP34,JP17,JP67,JP68,JP136,JP118,JP33,JP85,JP84,JP51,JP102,JP50,JP135,JP16";"MICRO-FIDUCIAL";16;"FIDUCIALUFIDUCIAL";;;
9;"U40,U7,U25,U42,U127,U15,U59,U38,U60,U78,U3,U43,U55,U110,U96,U129,U73,U22,U37,U57,U98,U92,U113,U21,U95,U133,U116,U44,U109,U111,U80,U24,U74,U115,U79,U77,U1,U61,U41,U76,U19,U91,U56,U62,U39,U20,U75,U114,U128,U5,U93,U94,U130,U134,U26,U13,U131,U58,U11,U132,U9,U112,U97,U23";"DIP8SMD";64;"MOC3063S";;;
10;"U88,U10,U83,U68,U139,U106,U86,U72,U141,U102,U51,U65,U142,U104,U144,U103,U87,U69,U34,U49,U14,U121,U36,U8,U12,U66,U33,U31,U2,U52,U84,U105,U90,U122,U67,U123,U32,U54,U16,U6,U107,U85,U35,U108,U71,U53,U126,U89,U124,U119,U137,U29,U140,U125,U70,U4,U50,U120,U143,U48,U30,U138,U47,U101";"SOT223";64;"Z0103MN";;;
11;"JP19,CHAN_D0,JP104,CHAN_E3,CHAN_F3,CHAN_A0,JP14,JP87,JP69,JP35,CHAN_A1,CHAN_C6,CHAN_G5,CHAN_D3,CHAN_F6,CHAN_H5,JP53,CHAN_B3,CHAN_C1,CHAN_E5,CHAN_A2,CHAN_F0,CHAN_D2,CHAN_D7,CHAN_C7,CHAN_F4,CHAN_H7,CHAN_A3,CHAN_H1,CHAN_E2,JP121,CHAN_A5,JP120,CHAN_B4,CHAN_H3,CHAN_F2,CHAN_E7,JP18,JP52,CHAN_F7,CHAN_D4,CHAN_C5,CHAN_G4,CHAN_D1,CHAN_E6,CHAN_H6,CHAN_G2,CHAN_G0,CHAN_B6,CHAN_G6,JP70,JP103,CHAN_C0,CHAN_B1,CHAN_F1,JP36,CHAN_F5,CHAN_H0,CHAN_B2,CHAN_D6,CHAN_G3,CHAN_C2,CHAN_C4,CHAN_B7,CHAN_B5,CHAN_A4,CHAN_H4,CHAN_G1,JP11,CHAN_D5,CHAN_A7,CHAN_E1,CHAN_E0,CHAN_C3,CHAN_G7,CHAN_E4,JP86,CHAN_H2,CHAN_B0,CHAN_A6";"JST-2-SMD";80;"";;;
12;"C4,C16,C2,C14,C8,C10,C12,C6";"EIA3216";8;"10uF";;;
13;"D3,D8,D7,D5,D4,D6,D1,D2";"LED-0603";8;"Status";;;
14;"JP48,JP133,JP99,JP9,JP82,JP31,JP65,JP116,JP49,JP117,JP15,JP32,JP100,JP66,JP134,JP83";"SFE-NEW-WEBLOGO";16;"LOGO-SFENEW";;;
15;"SJ1,SJ6,SJ8,SJ5,SJ4,SJ2,SJ3,SJ7";"SJ_2S-NO";8;"";;;
16;"R230,R143,R201,R114,R172,R56,R85,R27";"0603-RES";8;"240";;;
17;"U$6,U$3,U$4,U$8,U$7,U$1,U$5,U$2";"OSHW-LOGO-S";8;"OSHW-LOGOS";;;
18;"U45,U17,U117,U135,U63,U27,U81,U99";"V-REG_DPACK";8;"LM317";;;
19;"U18,U28,U46,U100,U118,U136,U82,U64";"DUEMILANOVE_SHIELD_NOLABELS";8;"ARDUINO_SHIELD";;;
20;"E$5,E$6";"FIDUCIAL-1X2";2;"";;;
21;"E$1";"FIDUCIAL-1.5X3";1;"";;;

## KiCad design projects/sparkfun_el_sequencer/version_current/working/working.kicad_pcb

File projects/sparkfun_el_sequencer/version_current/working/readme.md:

# EL_Sequencer by sparkfun  
This is a harvested standardized copy of a project from github.  
The original project can be found at:  
https://github.com/sparkfun/EL_Sequencer  
Please consult that link for additional, details, files, and license information.  
Note: It was auto harvested and if the original repo had more than one board file or anything out of the ordinary the files here are likely not representative.

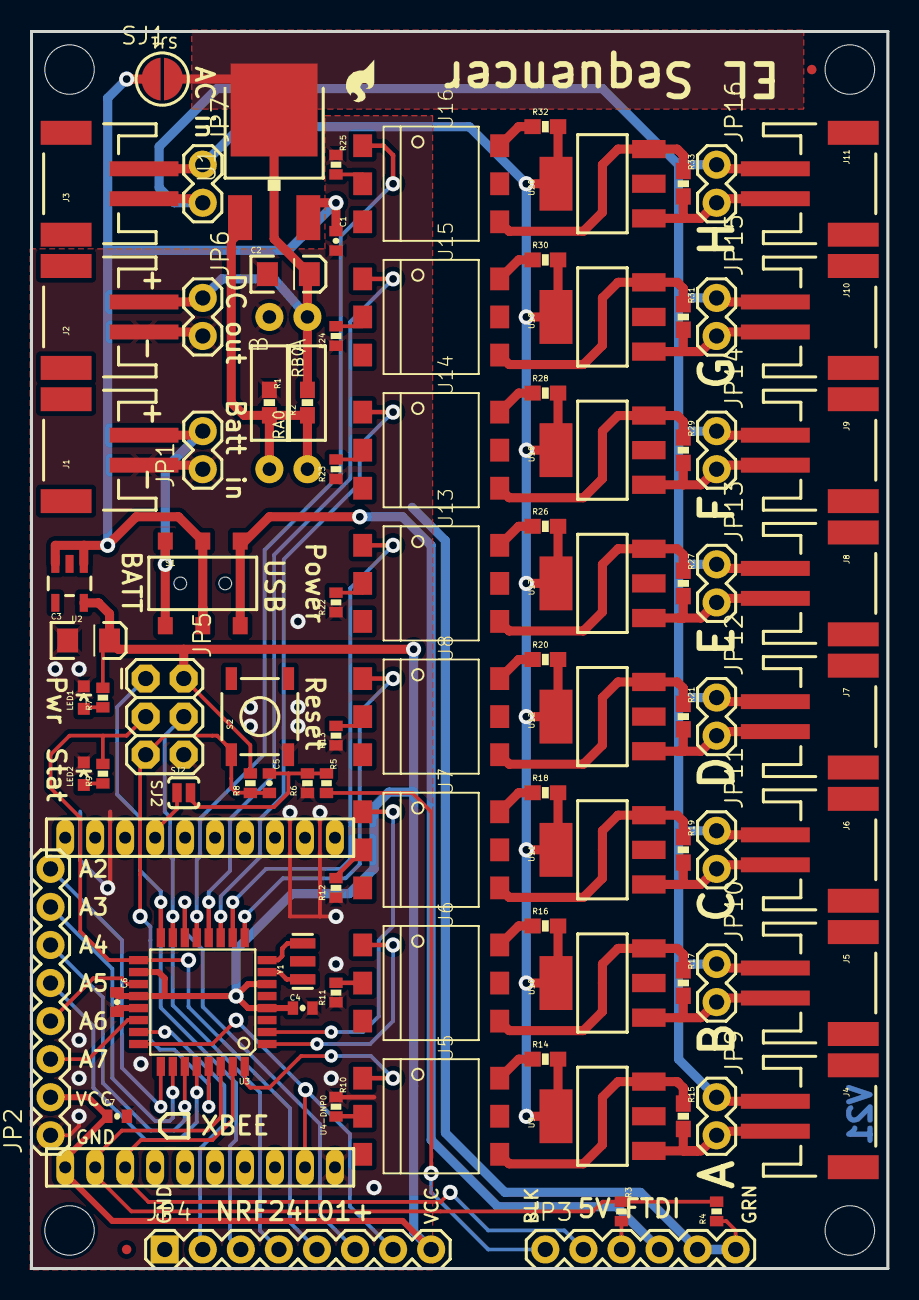
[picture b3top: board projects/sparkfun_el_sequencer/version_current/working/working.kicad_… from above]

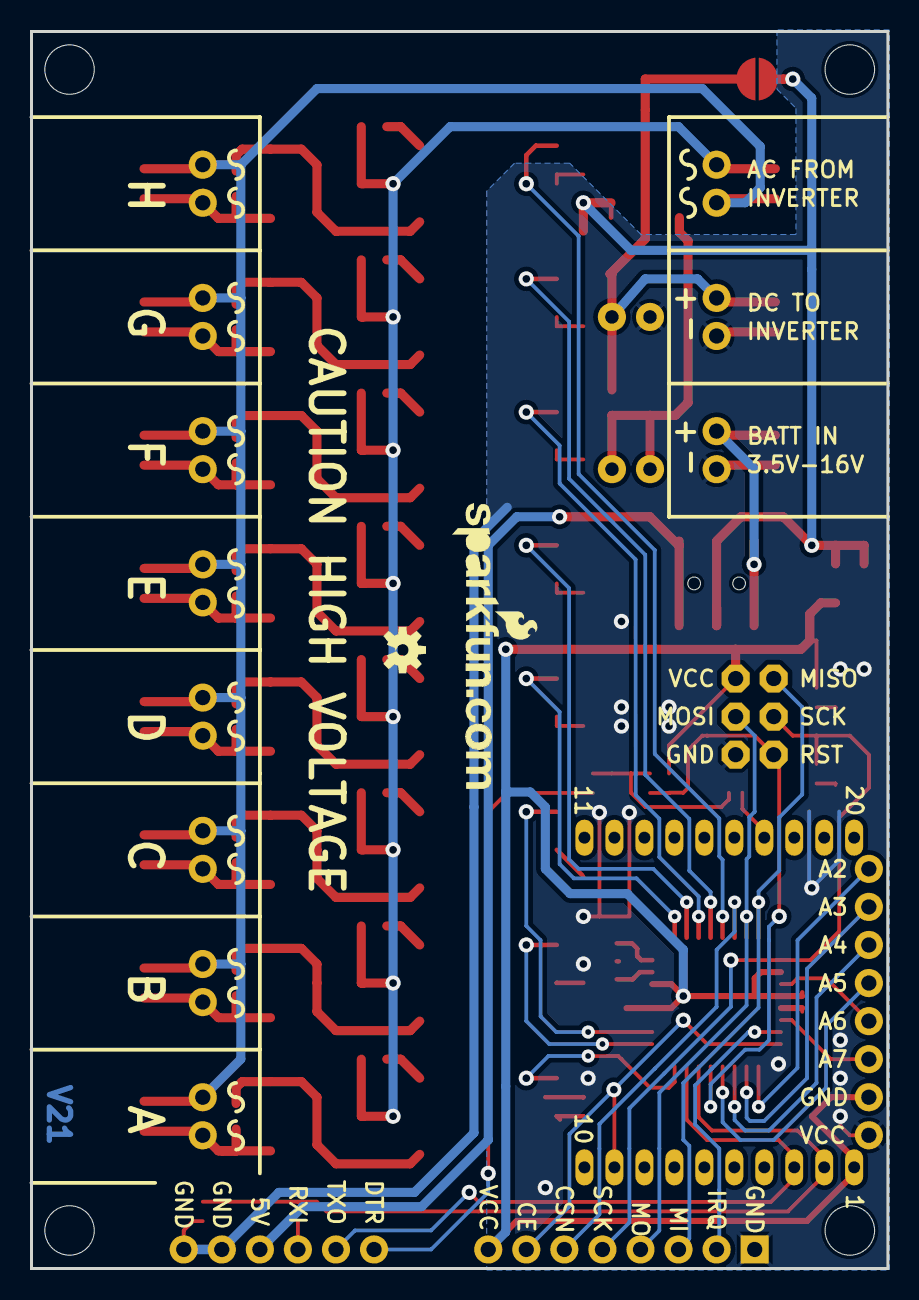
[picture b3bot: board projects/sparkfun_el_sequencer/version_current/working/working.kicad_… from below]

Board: 2 copper layers, 57.1 x 82.6 mm, 106 parts (2 on the bottom side), 72 nets.

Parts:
C1, C4, C5, C6, C7: 0.1uF; 0402-CAP
C2, C3: 10uF; EIA3216
FRAME1, FRAME2: FRAME-LETTER; CREATIVE_COMMONS
J1: Battery; JST-2-SMD
J2: DC-OUTPUT; JST-2-SMD
J3: AC-INPUT; JST-2-SMD
J4, J5, J6, J7, J8, J9, J10, J11: JST-2-SMD
JP1, JP6, JP7, JP9, JP10, JP11, JP12, JP13, JP14, JP15, JP16: 1X02
JP2: I/O; 1X08_ROUND
JP3: 5V_FTDI; 1X06
JP4: nRF24L01; 1X08
JP5: PROG; 2X3
JP8: LOGO-SFESK; SFE-LOGO-FLAME
LED1: Power; LED-0603
LED2: Status; LED-0603
R1: 390; 0603-RES
R2: 240; 0603-RES
R3, R5, R7, R9: 1K; 0402-RES
R4, R6: 2K; 0402-RES
R8: 10K; 0402-RES
R10, R11, R12, R13, R22, R23, R24, R25: 390; 0402-RES
R14, R15, R16, R17, R18, R19, R20, R21, R26, R27, R28, R29, R30, R31, R32, R33: 330; 0603-RES
RA0: A; AXIAL-0.4
RB0: B; AXIAL-0.4
S1: POWER; AYZ0202
S2: RESET; TACTILE_SWITCH_SMD
SJ1: SJ_ROUND
SJ2: SJ_2S-NO
U1: LM317; V-REG_DPACK
U2: MIC5219-3.3; SOT23-5
U3: ATMEGA328P; TQFP32-08
U4-DNP0: XBEE HEADER; XBEE-LONGPAD
U5, U6, U7, U8, U13, U14, U15, U16: MOC3063S; DIP8SMD
U9, U10, U11, U12, U17, U18, U19, U20: Z0103MN; SOT223
U$1: OSHW-LOGOS; OSHW-LOGO-S
U$2: LOGO-SFENEW; SFE-NEW-WEBLOGO
U$3, U$4: FIDUCIALUFIDUCIAL; MICRO-FIDUCIAL
U$5, U$6, U$7, U$8: STAND-OFF
Y1: 8MHz; RESONATOR-SMD

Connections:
5VUSB: JP3.4, S1.3, S1.6
ADC_2: JP2.8, U3.25
ADC_3: JP2.7, U3.26
ADC_4: JP2.6, U3.27
ADC_5: JP2.5, U3.28
ADC_6*: JP2.4, U3.19
ADC_7*: JP2.3, U3.22
CE/SLEEP: JP4.7, U3.24, U4-DNP0.9
CSN: JP4.6, U3.14
DTR: C5.1, R5.1, R6.2, SJ2.2
EL_A: U3.32, U5.1
EL_B: U3.1, U6.1
EL_C: U3.2, U7.1
EL_D: U3.9, U8.1
EL_E: U3.10, U13.1
EL_F: U3.11, U14.1
EL_G: U3.12, U15.1
EL_H: U3.13, U16.1
FTDI_DTR: JP3.1, R5.2
FTDI_RXI: JP3.3, R3.2
GND: C1.2, C2.C, C3.C, C4.2, C6.2, C7.2, J1.1, J2.1, JP1.1, JP2.1, JP3.5, JP3.6, JP4.1, JP5.6, JP6.2, LED1.C, LED2.C, R1.1, R4.1, R6.1, R10.1, R11.1, R12.1, R13.1, R22.1, R23.1, R24.1, R25.1, RB0.P$1, S2.3, U2.2, U3.3, U3.5, U3.21, U4-DNP0.10, Y1.2
HV: J3.2, JP7.1, R14.2, R16.2, R18.2, R20.2, R26.2, R28.2, R30.2, R32.2, U9.4, U10.4, U11.4, U12.4, U17.4, U18.4, U19.4, U20.4
HVGND: J3.1, J4.1, J5.1, J6.1, J7.1, J8.1, J9.1, J10.1, J11.1, JP7.2, JP9.1, JP10.1, JP11.1, JP12.1, JP13.1, JP14.1, JP15.1, JP16.1
INV: C2.A, J2.2, JP6.1, R2.2, RA0.P$2, SJ1.2, U1.4
IRQ: JP4.2, U3.23
MISO: JP4.3, JP5.1, U3.16
MOSI: JP4.4, JP5.4, U3.15
unnamed: U3.7, Y1.1
unnamed: R17.1, U6.4, U10.3
unnamed: R11.2, U6.2
unnamed: LED1.A, R7.1
unnamed: R16.1, U6.6
unnamed: U3.8, Y1.3
unnamed: R10.2, U5.2
unnamed: SJ2.1, U4-DNP0.17
unnamed: J5.2, JP10.2, R17.2, U10.1
unnamed: R19.1, U7.4, U11.3
unnamed: R14.1, U5.6
unnamed: R12.2, U7.2
unnamed: R1.2, R2.1, RA0.P$1, RB0.P$2, U1.1
unnamed: LED2.A, R9.1
unnamed: R18.1, U7.6
unnamed: J6.2, JP11.2, R19.2, U11.1
unnamed: R21.1, U8.4, U12.3
unnamed: R13.2, U8.2
unnamed: R20.1, U8.6
unnamed: J7.2, JP12.2, R21.2, U12.1
unnamed: J4.2, JP9.2, R15.2, U9.1
unnamed: R27.1, U13.4, U17.3
unnamed: R22.2, U13.2
unnamed: R26.1, U13.6
unnamed: J8.2, JP13.2, R27.2, U17.1
unnamed: R29.1, U14.4, U18.3
unnamed: R23.2, U14.2
unnamed: R28.1, U14.6
unnamed: J9.2, JP14.2, R29.2, U18.1
unnamed: R31.1, U15.4, U19.3
unnamed: R24.2, U15.2
unnamed: R30.1, U15.6
unnamed: J10.2, JP15.2, R31.2, U19.1
unnamed: R33.1, U16.4, U20.3
unnamed: R25.2, U16.2
unnamed: R32.1, U16.6
unnamed: J11.2, JP16.2, R33.2, U20.1
unnamed: R15.1, U5.4, U9.3
RAW: C1.1, S1.2, S1.5, SJ1.1, U1.3, U2.1, U2.3
RST: C5.2, JP5.5, R8.1, S2.1, U3.29
RXI: R3.1, R4.2, U3.30, U4-DNP0.2
SCK: JP4.5, JP5.3, R9.2, U3.17
TXO: JP3.2, U3.31, U4-DNP0.3
VBATT: J1.2, JP1.2, S1.1, S1.4
VCC: C3.A, C4.1, C6.1, C7.1, JP2.2, JP4.8, JP5.2, R7.2, R8.2, U2.5, U3.4, U3.6, U3.18, U3.20, U4-DNP0.1

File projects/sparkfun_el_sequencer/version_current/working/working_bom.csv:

"Id";"Designator";"Footprint";"Quantity";"Designation";"Supplier and ref";
1;"R28,R26,R32,R21,R30,R29,R18,R16,R20,R17,R14,R15,R31,R19,R27,R33";"0603-RES";16;"330";;;
2;"U1";"V-REG_DPACK";1;"LM317";;;
3;"U$4,U$3";"MICRO-FIDUCIAL";2;"FIDUCIALUFIDUCIAL";;;
4;"R22,R11,R25,R10,R13,R24,R23,R12";"0402-RES";8;"390";;;
5;"U18,U10,U9,U19,U20,U12,U17,U11";"SOT223";8;"Z0103MN";;;
6;"R1";"0603-RES";1;"390";;;
7;"S2";"TACTILE_SWITCH_SMD";1;"RESET";;;
8;"SJ1";"SJ_ROUND";1;"";;;
9;"C1,C6,C4,C5,C7";"0402-CAP";5;"0.1uF";;;
10;"FRAME2,FRAME1";"CREATIVE_COMMONS";2;"FRAME-LETTER";;;
11;"R5,R9,R3,R7";"0402-RES";4;"1K";;;
12;"U$8,U$7,U$5,U$6";"STAND-OFF";4;"STAND-OFF";;;
13;"U4-DNP0";"XBEE-LONGPAD";1;"XBEE HEADER";;;
14;"JP10,JP1,JP14,JP6,JP12,JP16,JP13,JP11,JP7,JP9,JP15";"1X02";11;"";;;
15;"J3";"JST-2-SMD";1;"AC-INPUT";;;
16;"RB0";"AXIAL-0.4";1;"B";;;
17;"JP2";"1X08_ROUND";1;"I/O";;;
18;"JP5";"2X3";1;"PROG";;;
19;"U13,U16,U7,U8,U15,U5,U6,U14";"DIP8SMD";8;"MOC3063S";;;
20;"JP3";"1X06";1;"5V_FTDI";;;
21;"J2";"JST-2-SMD";1;"DC-OUTPUT";;;
22;"S1";"AYZ0202";1;"POWER";;;
23;"R2";"0603-RES";1;"240";;;
24;"R8";"0402-RES";1;"10K";;;
25;"J10,J7,J6,J9,J11,J8,J5,J4";"JST-2-SMD";8;"";;;
26;"JP8";"SFE-LOGO-FLAME";1;"LOGO-SFESK";;;
27;"Y1";"RESONATOR-SMD";1;"8MHz";;;
28;"SJ2";"SJ_2S-NO";1;"";;;
29;"J1";"JST-2-SMD";1;"Battery";;;
30;"LED1";"LED-0603";1;"Power";;;
31;"JP4";"1X08";1;"nRF24L01";;;
32;"C2,C3";"EIA3216";2;"10uF";;;
33;"LED2";"LED-0603";1;"Status";;;
34;"R4,R6";"0402-RES";2;"2K";;;
35;"U2";"SOT23-5";1;"MIC5219-3.3";;;
36;"U3";"TQFP32-08";1;"ATMEGA328P";;;
37;"RA0";"AXIAL-0.4";1;"A";;;
38;"U$2";"SFE-NEW-WEBLOGO";1;"LOGO-SFENEW";;;
39;"U$1";"OSHW-LOGO-S";1;"OSHW-LOGOS";;;
